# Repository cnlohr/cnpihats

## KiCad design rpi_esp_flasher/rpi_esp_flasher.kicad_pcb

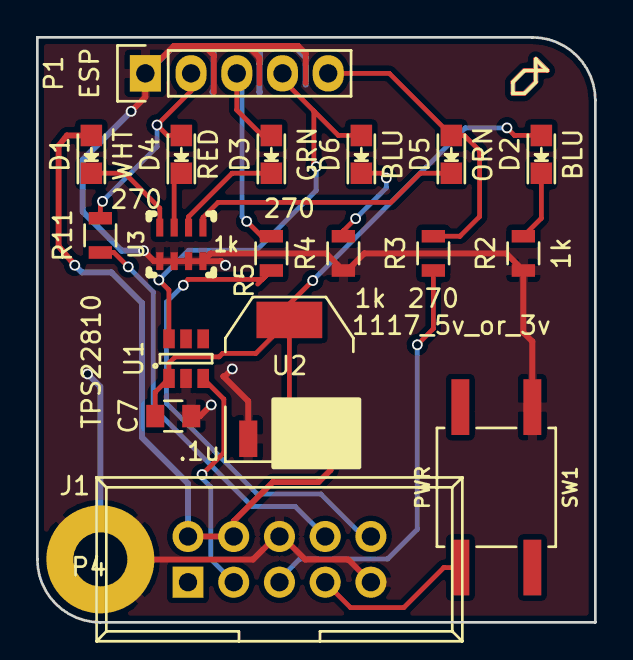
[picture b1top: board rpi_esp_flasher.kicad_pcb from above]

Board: 2 copper layers, 31.0 x 32.5 mm, 19 parts (0 on the bottom side), 18 nets.

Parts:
C7: .1u; C_0805
D1: WHT; LED_0805
D2, D6: BLU; LED_0805
D3: GRN; LED_0805
D4: RED; LED_0805
D5: ORN; LED_0805
J1: Raspberry_Pi_2_3; IDC_Header_Straight_10pins
P1: ESP; Pin_Header_Straight_1x05
P4: CONN_1; MountingHole_3mm_Pad
R2, R4: 1k; R_0805
R3, R5, R11: 270; R_0805
SW1: PWR; TACTILE10
U1: TPS22810; SOT-23-6
U2: 1117_5v_or_3v; SOT-223
U3: 1k; NETWORK1206

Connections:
GND: C7.1, J1.6, J1.9, P1.1, P4.1, R2.1, R4.1, SW1.1, U1.2, U2.1, U3.5, U3.6, U3.7, U3.8
GPIO2: J1.3, U1.3
GPIO3: D5.2, P1.5, R3.2
GPIO4: J1.7, SW1.4
LRX: D3.2, P1.3, R5.2
LTX: D4.2, P1.2, R11.2
unnamed: C7.2, D2.2, U1.1, U2.2, U2.4
unnamed: D1.1, U3.4
unnamed: D2.1, R2.2
unnamed: D3.1, U3.2
unnamed: D4.1, U3.3
unnamed: D5.1, U3.1
unnamed: D6.1, R4.2
unnamed: D6.2, P1.4, U1.6
unnamed: J1.5, R3.1
unnamed: J1.8, R11.1
unnamed: J1.10, R5.1
PI_PWR: D1.2, J1.2, J1.4, U2.3

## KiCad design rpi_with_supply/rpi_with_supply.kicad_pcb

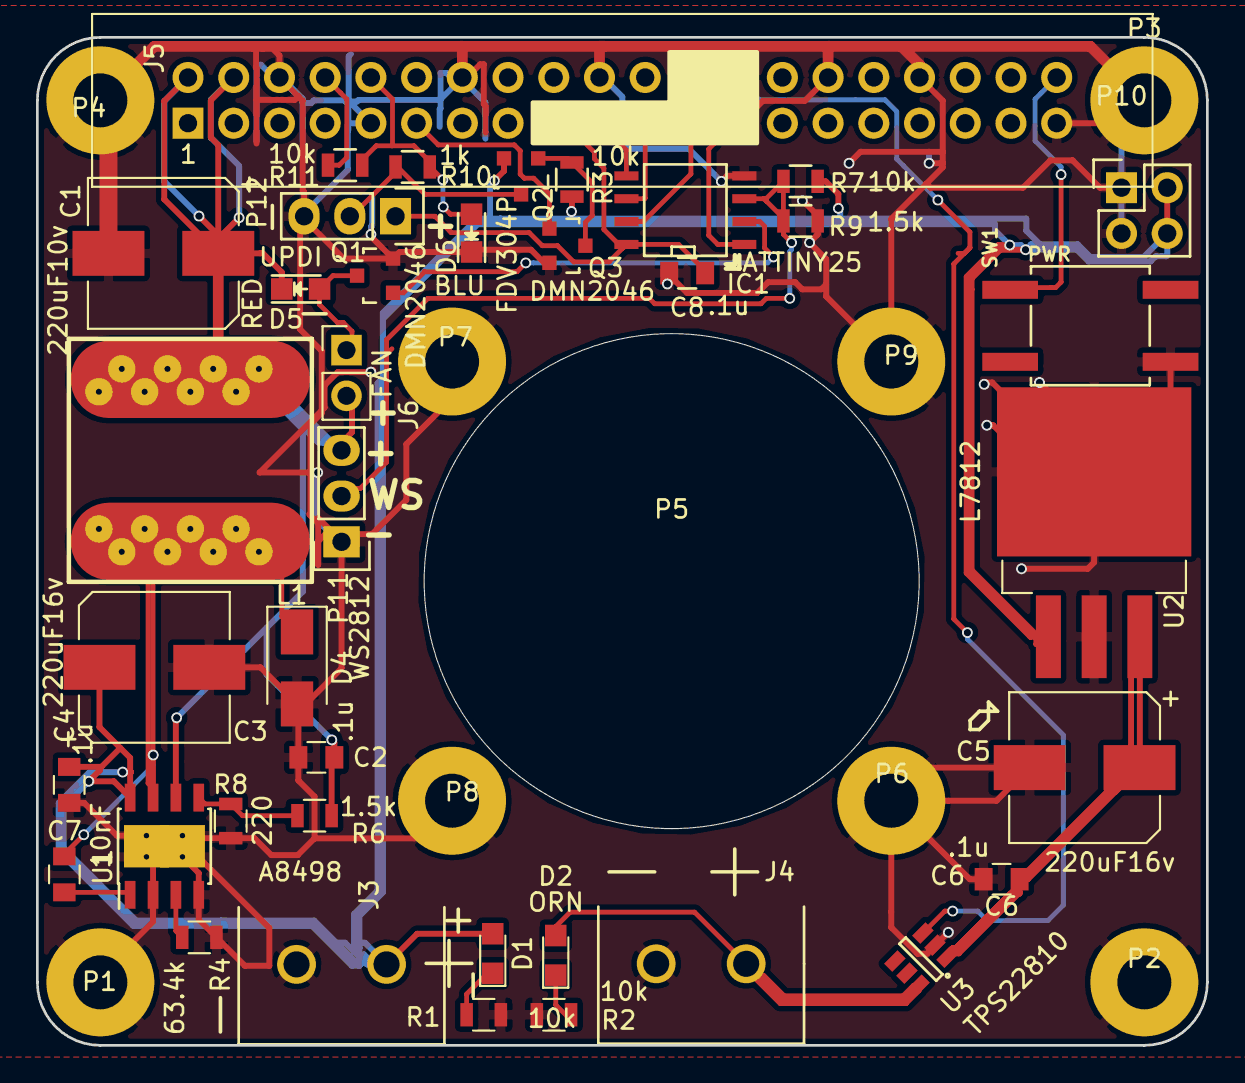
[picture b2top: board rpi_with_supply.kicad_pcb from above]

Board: 2 copper layers, 65.0 x 56.0 mm, 48 parts (0 on the bottom side), 26 nets.

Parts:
C1: 220uF10v; CP_Elec_8x6.7
C2, C4, C6, C8: .1u; C_0805
C3, C5: 220uF16v; CP_Elec_8x6.7
C7: 10nF; C_0805
D1, D5: RED; LED_0805
D2: ORN; LED_0805
D4: D_Schottky; D_SMA
D6: BLU; LED_0805
IC1: ATTINY25; SOIC-8-WIDE
J3, J4: Phoenix 1933189 COMBICON; PHOENIX1933189
J5: Raspberry_Pi_2_3; IDC_Header_Straight_40pins
J6: FAN; Socket_Strip_Straight_1x02_Pitch2.54mm
L1: 68uH; CHARLES_INDUCTOR
P1, P2, P3, P4, P5, P6, P7, P8, P9: CONN_1; MountingHole_3mm_Pad
P10: CONN_02X02; Pin_Header_Straight_2x02
P11: WS2812; Pin_Header_Straight_1x03
P12: UPDI; Pin_Header_Straight_1x03
Q1, Q3: DMN2046; SOT-23
Q2: FDV304P; SOT-23
R1, R2, R3, R7, R11: 10k; R_0805
R4: 63.4k; R_0805
R6, R9: 1.5k; R_0805
R8: 220; R_0805
R10: 1k; R_0805
SW1: PWR; TACTILE10
U1: A8498; SOIC-8-EP-THRU
U2: L7812; TO-263-3Lead
U3: TPS22810; SOT-23-6

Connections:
+3V3: C8.1, IC1.8, J5.17, P12.1
+12V: C5.1, C6.1, U2.3, U3.1
FANCTL: IC1.2, Q1.1
GND: C1.2, C2.2, C3.2, C4.2, C5.2, C6.2, C8.2, D4.2, D6.1, IC1.4, J3.1, J4.1, J5.6, J5.9, J5.14, J5.20, J5.25, J5.30, J5.34, J5.39, P1.1, P2.1, P3.1, P4.1, P6.1, P7.1, P8.1, P9.1, P10.1, P10.3, P11.1, P12.3, Q1.2, Q3.2, R1.1, R2.1, R4.2, R8.1, R9.2, SW1.1, U1.2, U1.4, U1.9, U2.2, U3.2
GPIO17: J5.11, Q3.1
GPIO21: J5.40, SW1.4
HT: C3.1, C4.1, D1.2, J3.2, P10.2, P10.4, Q2.2, R3.2, R7.1, U1.8, U2.1
INPUT: J5.26, U3.3
MISO: IC1.6, J5.21
MOSI: IC1.5, J5.19
unnamed: C7.1, D4.1, L1.1, U1.7
unnamed: C7.2, U1.1
unnamed: D1.1, R1.2
unnamed: D2.1, R2.2
unnamed: D5.2, J6.1, Q1.3
unnamed: IC1.3, P11.2, R7.2, R9.1
unnamed: J5.8, R11.1
unnamed: P12.2, Q2.3, R10.2
unnamed: Q2.1, Q3.3, R3.1
unnamed: R4.1, U1.3
unnamed: R6.1, R8.2, U1.5
OUT: D2.2, J4.2, U3.6
PI_PWR: C1.1, C2.1, D5.1, J5.2, J5.4, J6.2, L1.2, P11.3, R6.2, U1.6
SCK: IC1.7, J5.23
TXRX: D6.2, J5.10, R10.1, R11.2
~AVRRST~: IC1.1, J5.24

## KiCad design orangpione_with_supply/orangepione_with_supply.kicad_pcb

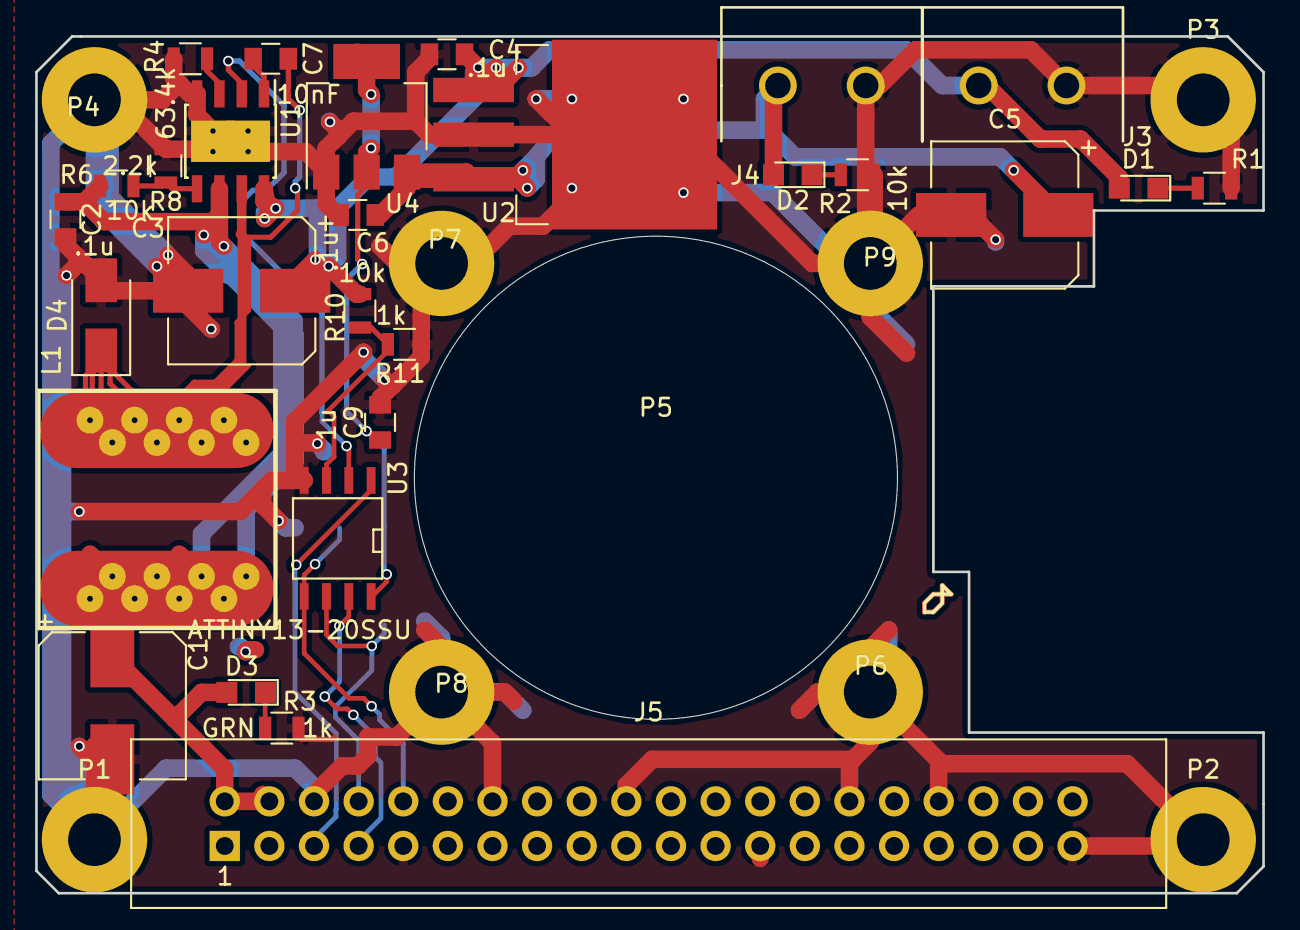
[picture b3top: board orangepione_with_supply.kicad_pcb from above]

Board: 2 copper layers, 69.9 x 48.8 mm, 38 parts (1 on the bottom side), 18 nets.

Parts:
C1, C3, C5: 220uF; CP_Elec_8x6.7
C2, C4, C6: .1u; C_0805
C7: 10nF; C_0805
C9: 1u; C_0805
D1: RED; LED_0805
D2: ORN; LED_0805
D3: GRN; LED_0805
D4: D_Schottky; D_SMA
J3, J4: Phoenix 1933189 COMBICON; PHOENIX1933189
J5: Raspberry_Pi_2_3; IDC_Header_Straight_40pins
J7: AVRISP6; RIBBON6SMT
L1: 68uH; CHARLES_INDUCTOR
P1, P2, P3, P4, P5, P6, P7, P8, P9: CONN_1; MountingHole_3mm_Pad
R1, R2, R6, R10: 10k; R_0805
R3, R11: 1k; R_0805
R4: 63.4k; R_0805
R8: 2.2k; R_0805
U1: A8498; SOIC-8-EP-THRU
U2: L7812; TO-263-3Lead
U3: ATTINY13-20SSU; SO8WIDE
U4: AP1117; SOT-223

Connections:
+5V: C9.1, J7.2, U3.8, U4.2, U4.4
+12V: C5.1, C6.1, D2.2, J4.2, U2.3, U4.3
GND: C1.2, C2.2, C3.2, C4.2, C5.2, C6.2, C9.2, D4.2, J3.1, J4.1, J5.6, J5.9, J5.14, J5.20, J5.25, J5.30, J5.34, J5.39, J7.6, P1.1, P2.1, P3.1, P4.1, P6.1, P7.1, P8.1, P9.1, R1.1, R2.1, R3.2, R4.2, R8.1, R11.2, U1.4, U1.9, U2.2, U3.4, U4.1
HT: C3.1, C4.1, D1.2, J3.2, R10.1, U1.8, U2.1
MISO: J5.8, J7.1, U3.6
MOSI: J5.10, J7.4, U3.5
unnamed: C7.1, D4.1, L1.1, U1.7
unnamed: C7.2, U1.1
unnamed: D1.1, R1.2
unnamed: D2.1, R2.2
unnamed: D3.1, R3.1
unnamed: R4.1, U1.3
unnamed: R6.1, R8.2, U1.5
unnamed: R10.2, R11.1, U3.3
PI_PWR: C1.1, C2.1, D3.2, J5.2, J5.4, L1.2, R6.2, U1.6
PWR_ENB: U1.2, U3.2
RST: J5.5, J7.5, U3.1
SCK: J5.7, J7.3, U3.7

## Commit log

2018-04-12 add newest hat.
2018-06-22 Bump rpi
2018-08-07 bump to rev A
2018-08-07 update shcematic
2018-08-19 bump to rev b
2018-08-19 Bump design with pull up
2018-08-27 update design
2018-09-06 bump
2018-10-03 Bump - add program for AVR stuff
2018-10-24 Bump operations! Now can calibrate ATTiny13's.
2018-10-24 update firmware, etc.
2018-10-24 Bump - fix flashing tool to add more useful features
2018-10-24 fix timing
2018-10-25 Fix makefile for writing
2018-10-25 work further on system, allowing calibration of ATTiny25's
2018-10-25 bump design
2018-10-31 add exp flasher
2018-11-02 switch to LM5110
2018-11-02 update design with new switch
2018-11-02 Update revb with new switch
